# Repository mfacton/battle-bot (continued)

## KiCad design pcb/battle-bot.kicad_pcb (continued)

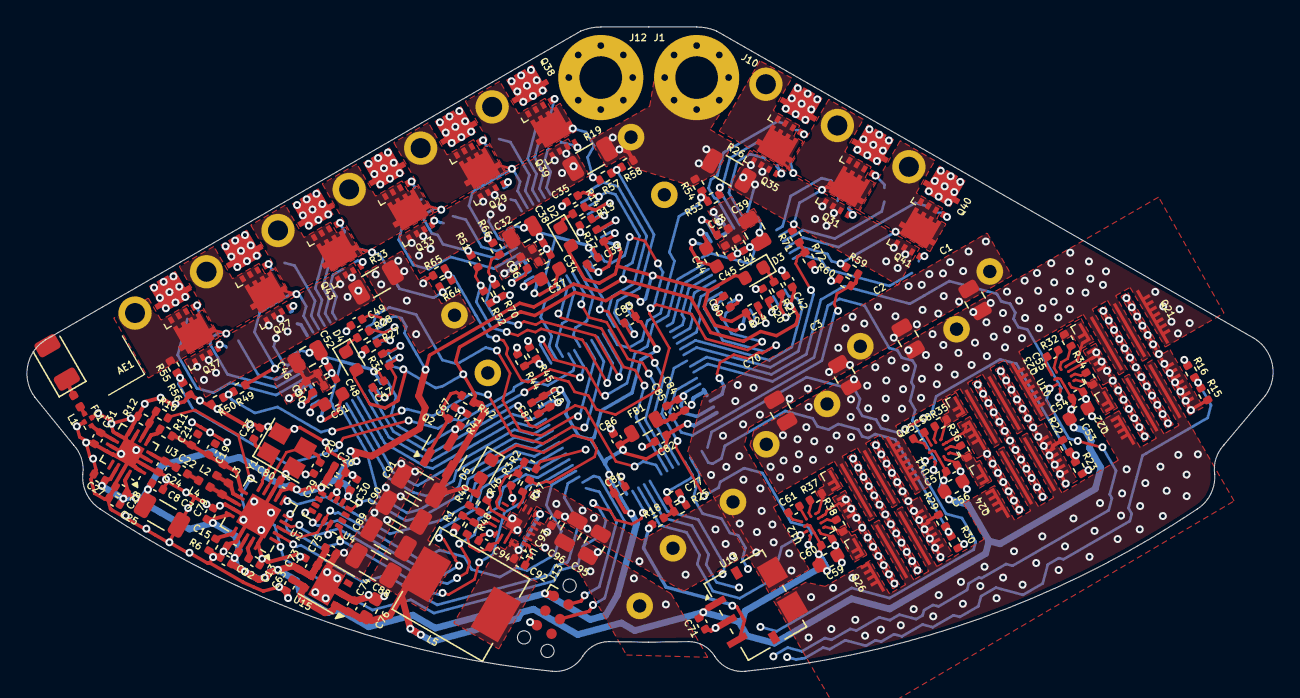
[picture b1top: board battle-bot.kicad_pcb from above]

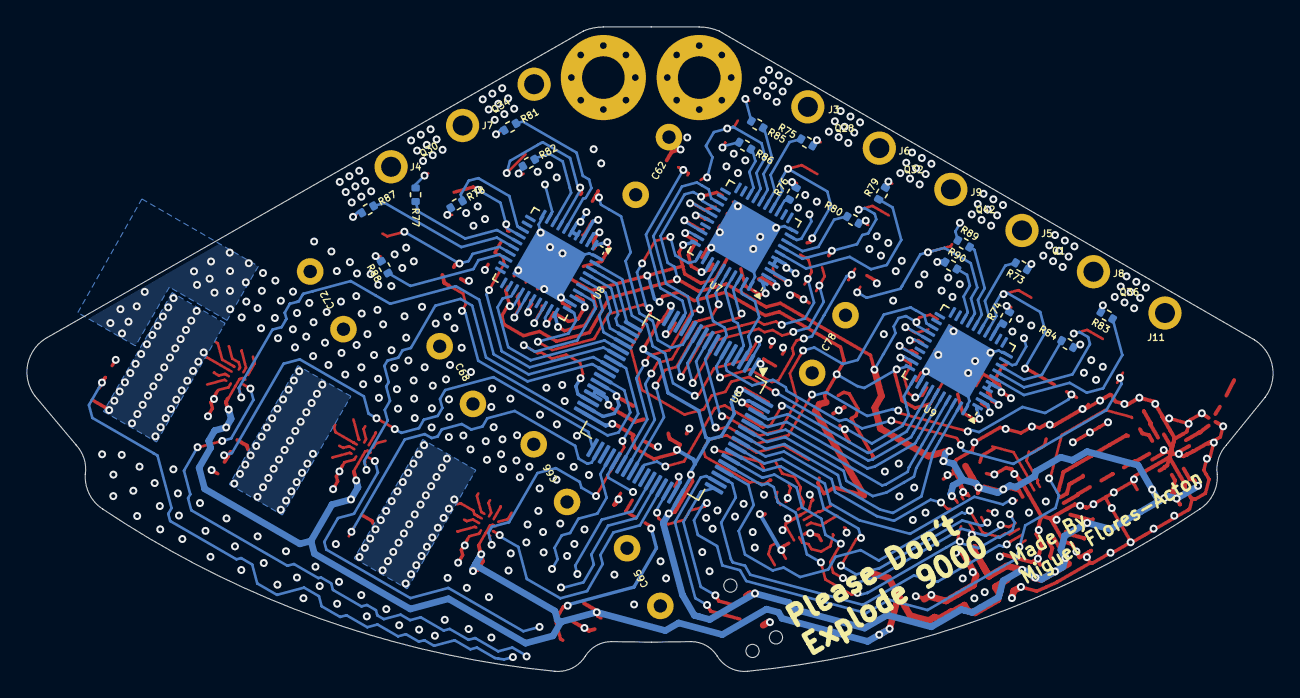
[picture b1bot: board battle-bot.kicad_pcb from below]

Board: 4 copper layers, 93.6 x 48.4 mm, 225 parts (28 on the bottom side), 172 nets.

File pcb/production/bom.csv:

Designator,Footprint,Quantity,Value,LCSC Part #
AE1,Johanson_2450AT18x100,1,Antenna_Chip,C127629
"C1, C2, C3, C32, C39, C46, C70, C95, C96",0805,9,22u,C45783
"C10, C25, C73",0402,3,10u,C15525
"C12, C27, C79, C80",0402,4,10n,C15195
"C13, C29, C30, C35, C42, C49, C54, C57, C60, C63, C71, C74, C75, C81, C82, C83, C84, C87, C92",0402,19,100n,C1525
C15,0402,1,1n,C1523
C19,0402,1,2n2,C1531
"C20, C23",0402,2,12p,C1547
C21,0402,1,4p7,C1569
C22,0402,1,1p5,C1552
C24,0402,1,1p,C1550
"C26, C67",0402,2,4u7,C23733
"C28, C77",0402,2,220p,C1530
C31,0402,1,0p3,C880415
"C33, C34, C36, C40, C41, C43, C47, C48, C50, C8, C85, C86, C94",0402,13,1u,C52923
"C37, C44, C51",0603,3,47n,C1622
"C38, C45, C52, C93",0402,4,100n,C307331
"C53, C56, C59, C76",0603,4,10u,C19702
"C55, C58, C61",0402,3,220n,C16772
"C62, C65, C66, C68, C72, C78",C_D10xL16_Horizontal,6,2m2,C5438720
C7,1206,1,100u,C15008
"C88, C89, C90, C91",1206,4,47u,C96123
"D2, D3, D4",0603,3,LEDR,C2286
D5,0603,1,LEDW,C2290
FB1,0805,1,FerriteBead,C1017
FL1,LFL152G45TC1A219,1,LFL152G45TC1A219,C91610
L1,0402,1,6n8,C82919
L2,0402,1,2n7,C162541
L3,0402,1,8n2,C84404
L4,0402,1,3n9,C14033
L5,L_Chilisin_BMRB00060618,1,2u2,C216189
"Q1, Q27, Q28, Q29, Q30, Q31, Q32, Q33, Q34, Q35, Q36, Q37, Q38, Q39, Q40, Q41, Q42, Q43",DFN3x3A_8L_EP1_P,18,AON7544,C315567
Q2,SOT-23,1,AO3401A,C15127
"R1, R3, R46, R49, R51, R53, R55, R57, R59, R64, R66, R71",0402,12,4k7,C25900
"R10, R11, R14, R21, R28, R41, R47, R50, R52, R54, R56, R58, R60, R65, R70, R72",0402,16,1k,C11702
"R12, R6",0402,2,22k,C25768
"R13, R20, R25, R27",0402,4,47k,C25792
"R15, R18, R22, R29",0402,4,10k,C25744
"R16, R23, R30",0402,3,1k5,C25867
"R17, R24, R31, R44",0402,4,15k,C25756
"R19, R26, R33",1206,3,2m,C601094
R2,0402,1,51k,C25794
"R32, R34, R35, R36, R37, R38, R73, R74, R75, R76, R77, R78, R79, R80, R81, R82, R83, R84, R85, R86, R87, R88, R89, R90",0402,24,10R,C25077
R40,0402,1,33k,C25779
"R42, R48",0402,2,100k,C25741
R45,0402,1,2k2,C25879
U1,VQFN-20_3x3mm_P0.45,1,TPS56C230,C1849534
"U10, U11, U12",LMG1205,3,LMG1205,C2653814
U13,Allegro_PSOF-7_4.8x6.4mm_P1.60mm,1,ACS780xLRTR-100B,C97317
U15,DFN-6-1EP_3x3mm_P0.95mm_EP1.7x2.6mm,1,LP38690SD,C130003
U2,QFN-20-1EP_4x4mm_P0.5mm_EP2.5x2.5mm,1,nRF24L01P,C8791
U3,QFN-16-1EP_3x3mm_P0.5mm_EP1.7x1.7mm,1,AT2401C,C783588
U4,LGA-14_3x2.5mm_P0.5mm_LayoutBorder3x4y,1,ICM-42688-P,C1850418
U6,LQFP-64_10x10mm_P0.5mm,1,STM32G431RBTx,C431633
"U7, U8, U9",HVQFN-40-1EP_6x6mm_P0.5mm_EP4.1x4.1mm,3,DRV8323H,C701783
Y1,Crystal_SMD_3225-4Pin_3.2x2.5mm,1,16MHz,C13738

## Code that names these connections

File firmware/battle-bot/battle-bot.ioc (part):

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Mcu.Name=STM32G431R(6-8-B)Tx
Mcu.Package=LQFP64
Mcu.UserName=STM32G431RBTx
PA0.Mode=IN1-Differential
PA0.Signal=ADC1_IN1
PA1.Mode=IN1-Differential
PA1.Signal=ADC1_IN2
PA10.Signal=S_TIM1_CH3
PA11.Signal=S_TIM1_CH4
PA12.Signal=GPIO_Output
PA13.Mode=Serial_Wire
PA13.Signal=SYS_JTMS-SWDIO
PA14.Mode=Serial_Wire
PA14.Signal=SYS_JTCK-SWCLK
PA15.Signal=GPIO_Output
PA2.Signal=ADC1_IN3
PA3.Signal=S_TIM15_CH2
PA4.Signal=GPIO_Output
PA5.Signal=S_TIM2_CH1
PA6.Signal=GPIO_Output
PA7.Signal=ADC2_IN4
PA9.Signal=S_TIM1_CH2
PB0.Mode=PWM Generation2 CH2 CH2N
PB0.Signal=TIM1_CH2N
PB1.Mode=PWM Generation3 CH3 CH3N
PB1.Signal=TIM1_CH3N
PB10.Signal=S_TIM2_CH3
PB11.Signal=ADC1_IN14
PB12.Mode=IN10-Differential
PB12.Signal=ADC1_IN11
PB14.Signal=ADC1_IN5
PB15.Signal=ADC2_IN15
PB2.Signal=ADC2_IN12
PB3.Signal=GPXTI3
PB4.Signal=GPXTI4
PB5.Signal=GPIO_Output
PB6.Signal=S_TIM4_CH1
PB7.Signal=GPIO_Output
PB8-BOOT0.Signal=S_TIM4_CH3
PB9.Signal=GPIO_Output
PC0.Signal=ADC1_IN6
PC1.Signal=ADC1_IN7
PC10.Mode=Full_Duplex_Master
PC10.Signal=SPI3_SCK
PC11.Mode=Full_Duplex_Master
PC11.Signal=SPI3_MISO
PC12.Mode=Full_Duplex_Master
PC12.Signal=SPI3_MOSI
PC13.Signal=GPIO_Output
PC14-OSC32_IN.Signal=GPIO_Output
PC15-OSC32_OUT.Signal=GPIO_Output
PC2.Mode=IN8-Differential
PC2.Signal=ADC1_IN8
PC3.Mode=IN8-Differential
PC3.Signal=ADC1_IN9
PC4.Signal=ADC2_IN5
PC5.Mode=PWM Generation4 CH4 CH4N
PC5.Signal=TIM1_CH4N
PC6.Signal=S_TIM3_CH1
PC7.Signal=S_TIM3_CH2
PC8.Signal=S_TIM3_CH3
PC9.Signal=S_TIM3_CH4
PD2.Signal=GPIO_Output
PF0-OSC_IN.Mode=IN10-Differential
PF0-OSC_IN.Signal=ADC1_IN10
PF1-OSC_OUT.Signal=ADC2_IN10
PG10-NRST.Signal=GPIO_Output
RCC.HSE_VALUE=16000000
RCC.SYSCLKFreq_VALUE=170000000
RCC.SYSCLKSource=RCC_SYSCLKSOURCE_PLLCLK
board=custom

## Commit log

2024-11-12 Add notes
2024-11-14 Save notes
2024-11-17 Make pcb
2024-11-17 Change parts
2024-11-22 Place power connectors
2024-11-23 Save
2024-11-24 Finish drivers
2024-11-26 Finish rough layout
2024-11-27 Save layout
2024-11-29 Save old buck regulator
2024-11-30 Finish pcb
2024-11-30 Save ioc
2024-12-05 Test save
2024-12-12 Update step
